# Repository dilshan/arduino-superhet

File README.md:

# Arduino Superheterodyne Receiver

In this project, we will upgrade a traditional shortwave [superheterodyne receiver](http://jayakody2000lk.blogspot.com/2015/03/two-transistor-superheterodyne.html) with an *[Arduino](https://store.arduino.cc/products/arduino-uno-rev3)* base tuner. This tuner is capable of receiving shortwave broadcasts on 41m band and above.

In this upgrade, we enhanced the local oscillator with [Si5351 clock generator module](https://s.click.aliexpress.com/e/_9iD0bV) and Arduino control circuit. Compared to the [old design](http://jayakody2000lk.blogspot.com/2015/03/two-transistor-superheterodyne.html), this new receiver uses an improved version of an intermediate frequency amplifier with 3 I.F transformers.

In this new design, we divide this receiver into several blocks, which include, mixer with a detector, a local oscillator, and an I.F amplifier. The I.F amplifier builds into one PCB. The filter stage, mixer, and detector stages place in another PCB.

In this prototype build, the *Si5351* clock generator drives using an *Arduino Uno* board. With the given sketch, the user can tune and switch the shortwave meter bands using a rotary encoder. The supplied sketch support clock generation from 5205kHz (tuner frequency : 4750kHz) to 16285kHz (tuner frequency : 15830kHz). If required, this range can further extend or reduce by modifying the Arduino source code. In the given source code, we use [*Etherkit's Si5351 library*](https://github.com/etherkit/Si5351Arduino) to control the clock generator module.

This receiver uses a conventional 455kHz I.F transformer kit in an intermediate frequency amplifier. We use a [2SC724](https://www.web-bcs.com/transistor/tc/2sc/2SC724.php) transistor for each filter stage. The value of this transistor is not critical and can be replaced with any suitable mid-frequency NPN transistor, for example, [2SC930](https://s.click.aliexpress.com/e/_9vi1D5), [BF494](https://s.click.aliexpress.com/e/_Ap8gur), [BC337](https://s.click.aliexpress.com/e/_9gRclD), or [2SC829](https://s.click.aliexpress.com/e/_ACedU7), etc.

The 2nd PCB consists of a filter, mixer, and detector circuit. This mixer stage also uses the NPN low power transistor and can replace with any of the above transistors. The crucial component of the detector phase is the [OA90](https://s.click.aliexpress.com/e/_AknfCT) or [1N34](https://s.click.aliexpress.com/e/_AdOUUn) Germanium diode. It can also change with any suitable Germanium signal diode. 

The front filter stage constructs using a pair of readymade [1µH inductors](https://s.click.aliexpress.com/e/_ApVWb9). The suggested supply voltage to this tuner is 6V to 9V. 

All the design files of this project were released under the [Creative Commons Attribution 4.0 International](https://creativecommons.org/licenses/by/4.0/) license. The Arduino sketch is released under the [MIT License](https://github.com/dilshan/arduino-superhet/blob/main/LICENSE).

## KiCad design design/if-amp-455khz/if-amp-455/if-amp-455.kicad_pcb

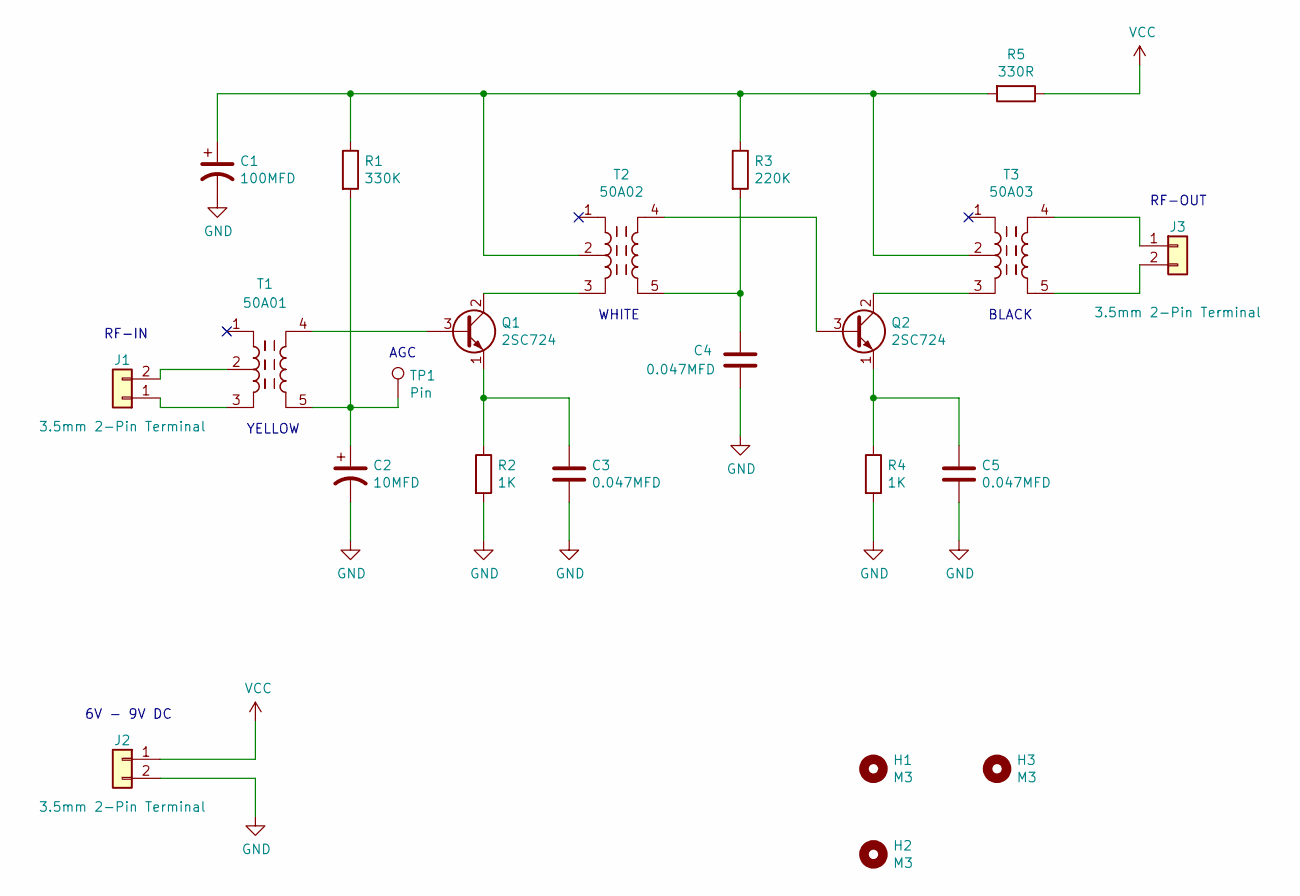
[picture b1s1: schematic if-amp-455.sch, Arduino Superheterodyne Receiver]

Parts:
C1: 100MFD; CP_Radial_D8.0mm_P3.80mm
C2: 10MFD; CP_Radial_D5.0mm_P2.50mm
C3, C4, C5: 0.047MFD; C_Disc_D7.0mm_W2.5mm_P5.00mm
H1, H2, H3: M3; MountingHole_3.2mm_M3
J1, J2, J3: 3.5mm 2-Pin Terminal; PhoenixContact_MCV_1,5_2-G-3.5_1x02_P3.50mm_Vertical
Q1, Q2: 2SC724; TO-92L_Inline_Wide
R1: 330K; R_Axial_DIN0207_L6.3mm_D2.5mm_P10.16mm_Horizontal
R2, R4: 1K; R_Axial_DIN0207_L6.3mm_D2.5mm_P10.16mm_Horizontal
R3: 220K; R_Axial_DIN0207_L6.3mm_D2.5mm_P10.16mm_Horizontal
R5: 330R; R_Axial_DIN0207_L6.3mm_D2.5mm_P10.16mm_Horizontal
T1: 50A01; 5-pin-if-transformer
T2: 50A02; 5-pin-if-transformer
T3: 50A03; 5-pin-if-transformer
TP1: Pin; TestPoint_Loop_D1.80mm_Drill1.0mm_Beaded

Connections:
GND: C1.2, C2.2, C3.2, C4.2, C5.2, J2.2, R2.2, R4.2, T1.6, T2.6, T3.6
unnamed: C1.1, R1.1, R3.1, R5.2, T2.2, T3.2
unnamed: C2.1, R1.2, T1.5, TP1.1
unnamed: C3.1, Q1.1 (E), R2.1
unnamed: C4.1, R3.2, T2.5
unnamed: C5.1, Q2.1 (E), R4.1
unnamed: J1.1, T1.3
unnamed: J1.2, T1.2
unnamed: J3.1, T3.4
unnamed: J3.2, T3.5
unnamed: Q1.2 (C), T2.3
unnamed: Q1.3 (B), T1.4
unnamed: Q2.2 (C), T3.3
unnamed: Q2.3 (B), T2.4
VCC: J2.1, R5.1

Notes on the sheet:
YELLOW
WHITE
BLACK
AGC
6V - 9V DC
RF-IN
RF-OUT

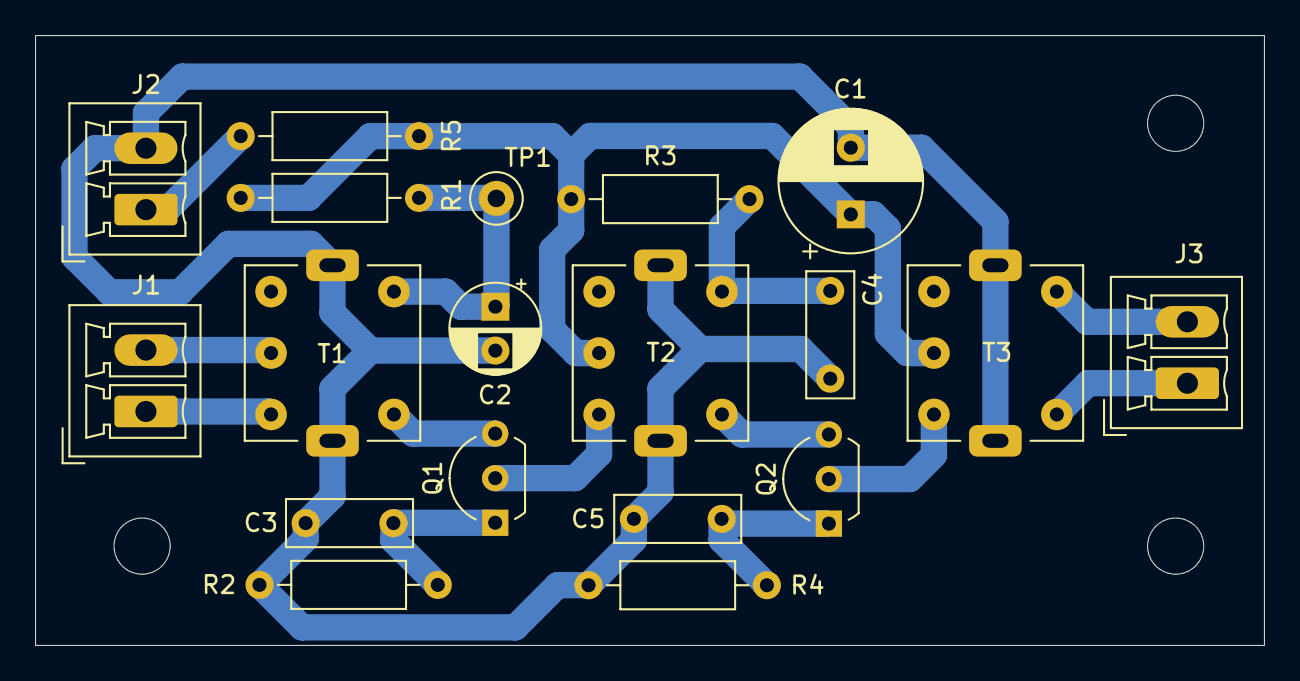
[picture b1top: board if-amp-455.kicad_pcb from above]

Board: 2 copper layers, 70.0 x 34.8 mm, 22 parts (0 on the bottom side), 15 nets.

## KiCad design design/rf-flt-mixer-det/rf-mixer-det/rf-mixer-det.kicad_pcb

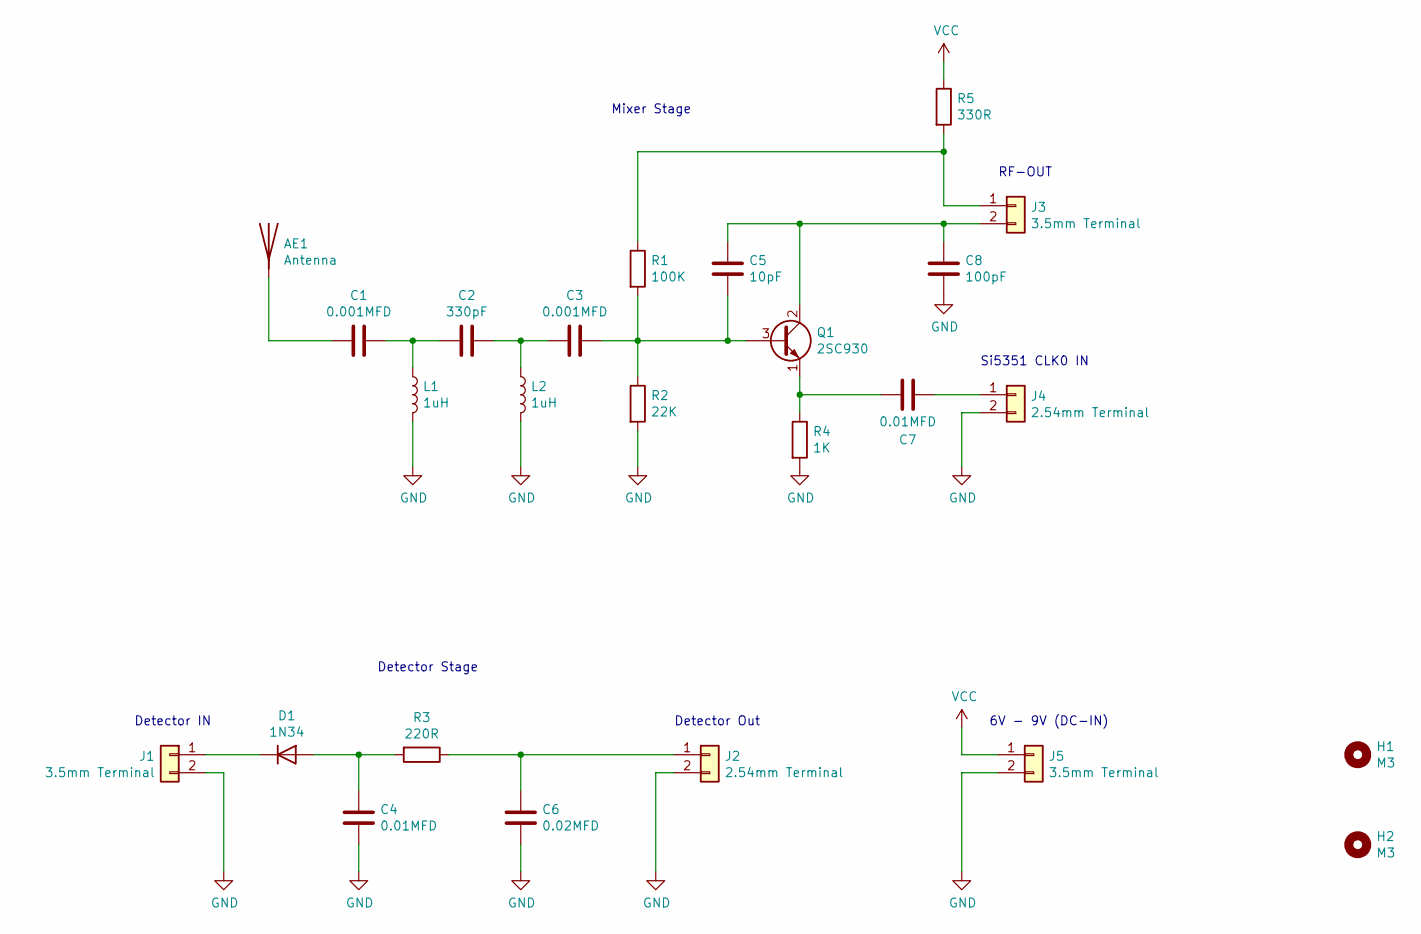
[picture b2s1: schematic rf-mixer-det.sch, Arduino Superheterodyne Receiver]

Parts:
AE1: Antenna; TestPoint_Loop_D1.80mm_Drill1.0mm_Beaded
C1, C3: 0.001MFD; C_Disc_D6.0mm_W2.5mm_P5.00mm
C2: 330pF; C_Disc_D5.1mm_W3.2mm_P5.00mm
C4, C7: 0.01MFD; C_Disc_D5.1mm_W3.2mm_P5.00mm
C5: 10pF; C_Disc_D5.1mm_W3.2mm_P5.00mm
C6: 0.02MFD; C_Disc_D5.1mm_W3.2mm_P5.00mm
C8: 100pF; C_Disc_D5.1mm_W3.2mm_P5.00mm
D1: 1N34; D_DO-34_SOD68_P10.16mm_Horizontal
H1, H2: M3; MountingHole_3.2mm_M3
J1, J3, J5: 3.5mm Terminal; PhoenixContact_MCV_1,5_2-G-3.5_1x02_P3.50mm_Vertical
J2, J4: 2.54mm Terminal; PinHeader_1x02_P2.54mm_Vertical
L1, L2: 1uH; L_Axial_L6.6mm_D2.7mm_P10.16mm_Horizontal_Vishay_IM-2
Q1: 2SC930; TO-92L_Inline_Wide
R1: 100K; R_Axial_DIN0207_L6.3mm_D2.5mm_P10.16mm_Horizontal
R2: 22K; R_Axial_DIN0207_L6.3mm_D2.5mm_P10.16mm_Horizontal
R3: 220R; R_Axial_DIN0207_L6.3mm_D2.5mm_P10.16mm_Horizontal
R4: 1K; R_Axial_DIN0207_L6.3mm_D2.5mm_P10.16mm_Horizontal
R5: 330R; R_Axial_DIN0207_L6.3mm_D2.5mm_P10.16mm_Horizontal

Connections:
GND: C4.2, C6.2, C8.2, J1.2, J2.2, J4.2, J5.2, L1.2, L2.2, R2.2, R4.2
unnamed: AE1.1, C1.2
unnamed: C1.1, C2.2, L1.1
unnamed: C2.1, C3.2, L2.1
unnamed: C3.1, C5.2, Q1.3 (B), R1.2, R2.1
unnamed: C4.1, D1.2 (A), R3.2
unnamed: C5.1, C8.1, J3.2, Q1.2 (C)
unnamed: C6.1, J2.1, R3.1
unnamed: C7.1, J4.1
unnamed: C7.2, Q1.1 (E), R4.1
unnamed: D1.1 (K), J1.1
unnamed: J3.1, R1.1, R5.2
VCC: J5.1, R5.1

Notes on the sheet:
Detector Stage
Mixer Stage
Detector IN
Detector Out
6V - 9V (DC-IN)
Si5351 CLK0 IN
RF-OUT

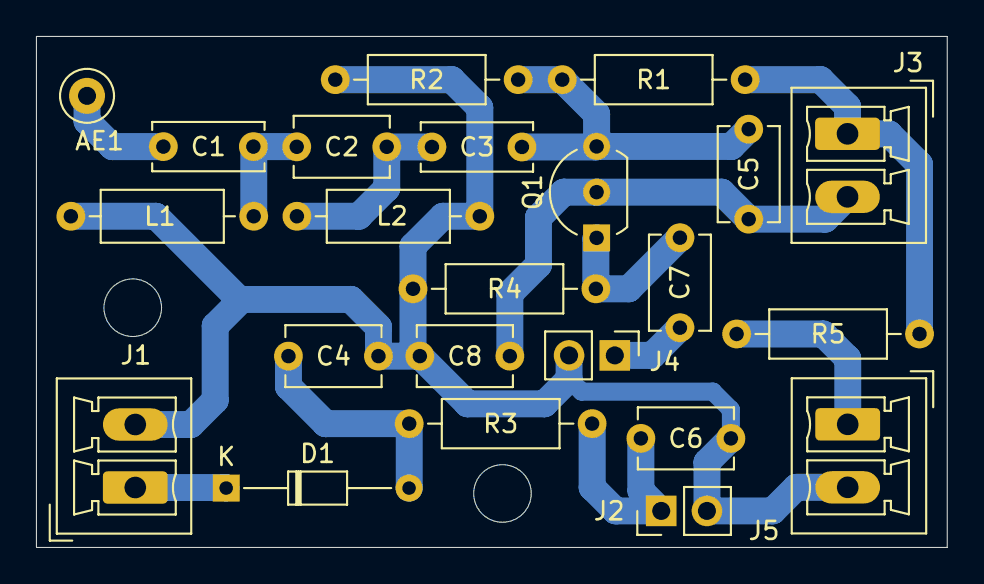
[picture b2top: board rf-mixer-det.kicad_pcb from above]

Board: 2 copper layers, 50.6 x 28.4 mm, 25 parts (0 on the bottom side), 13 nets.

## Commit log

2021-10-05 Initial version of source codes and design files.
2021-10-05 :art: Add images of the prototype builds.
2021-10-05 Minor style change in readme.md file.
2021-10-05 Add Youtube thumbnail image.
2021-10-05 Add Youtube thumbnail image into README.MD file.
2021-10-05 Fix formatting issues in README.MD file.
2021-10-07 Create CI script for the Arduino sketch.
2021-10-07 Update CI script to checkout all submodules.
2021-10-07 Fix video link in Readme.md file.
